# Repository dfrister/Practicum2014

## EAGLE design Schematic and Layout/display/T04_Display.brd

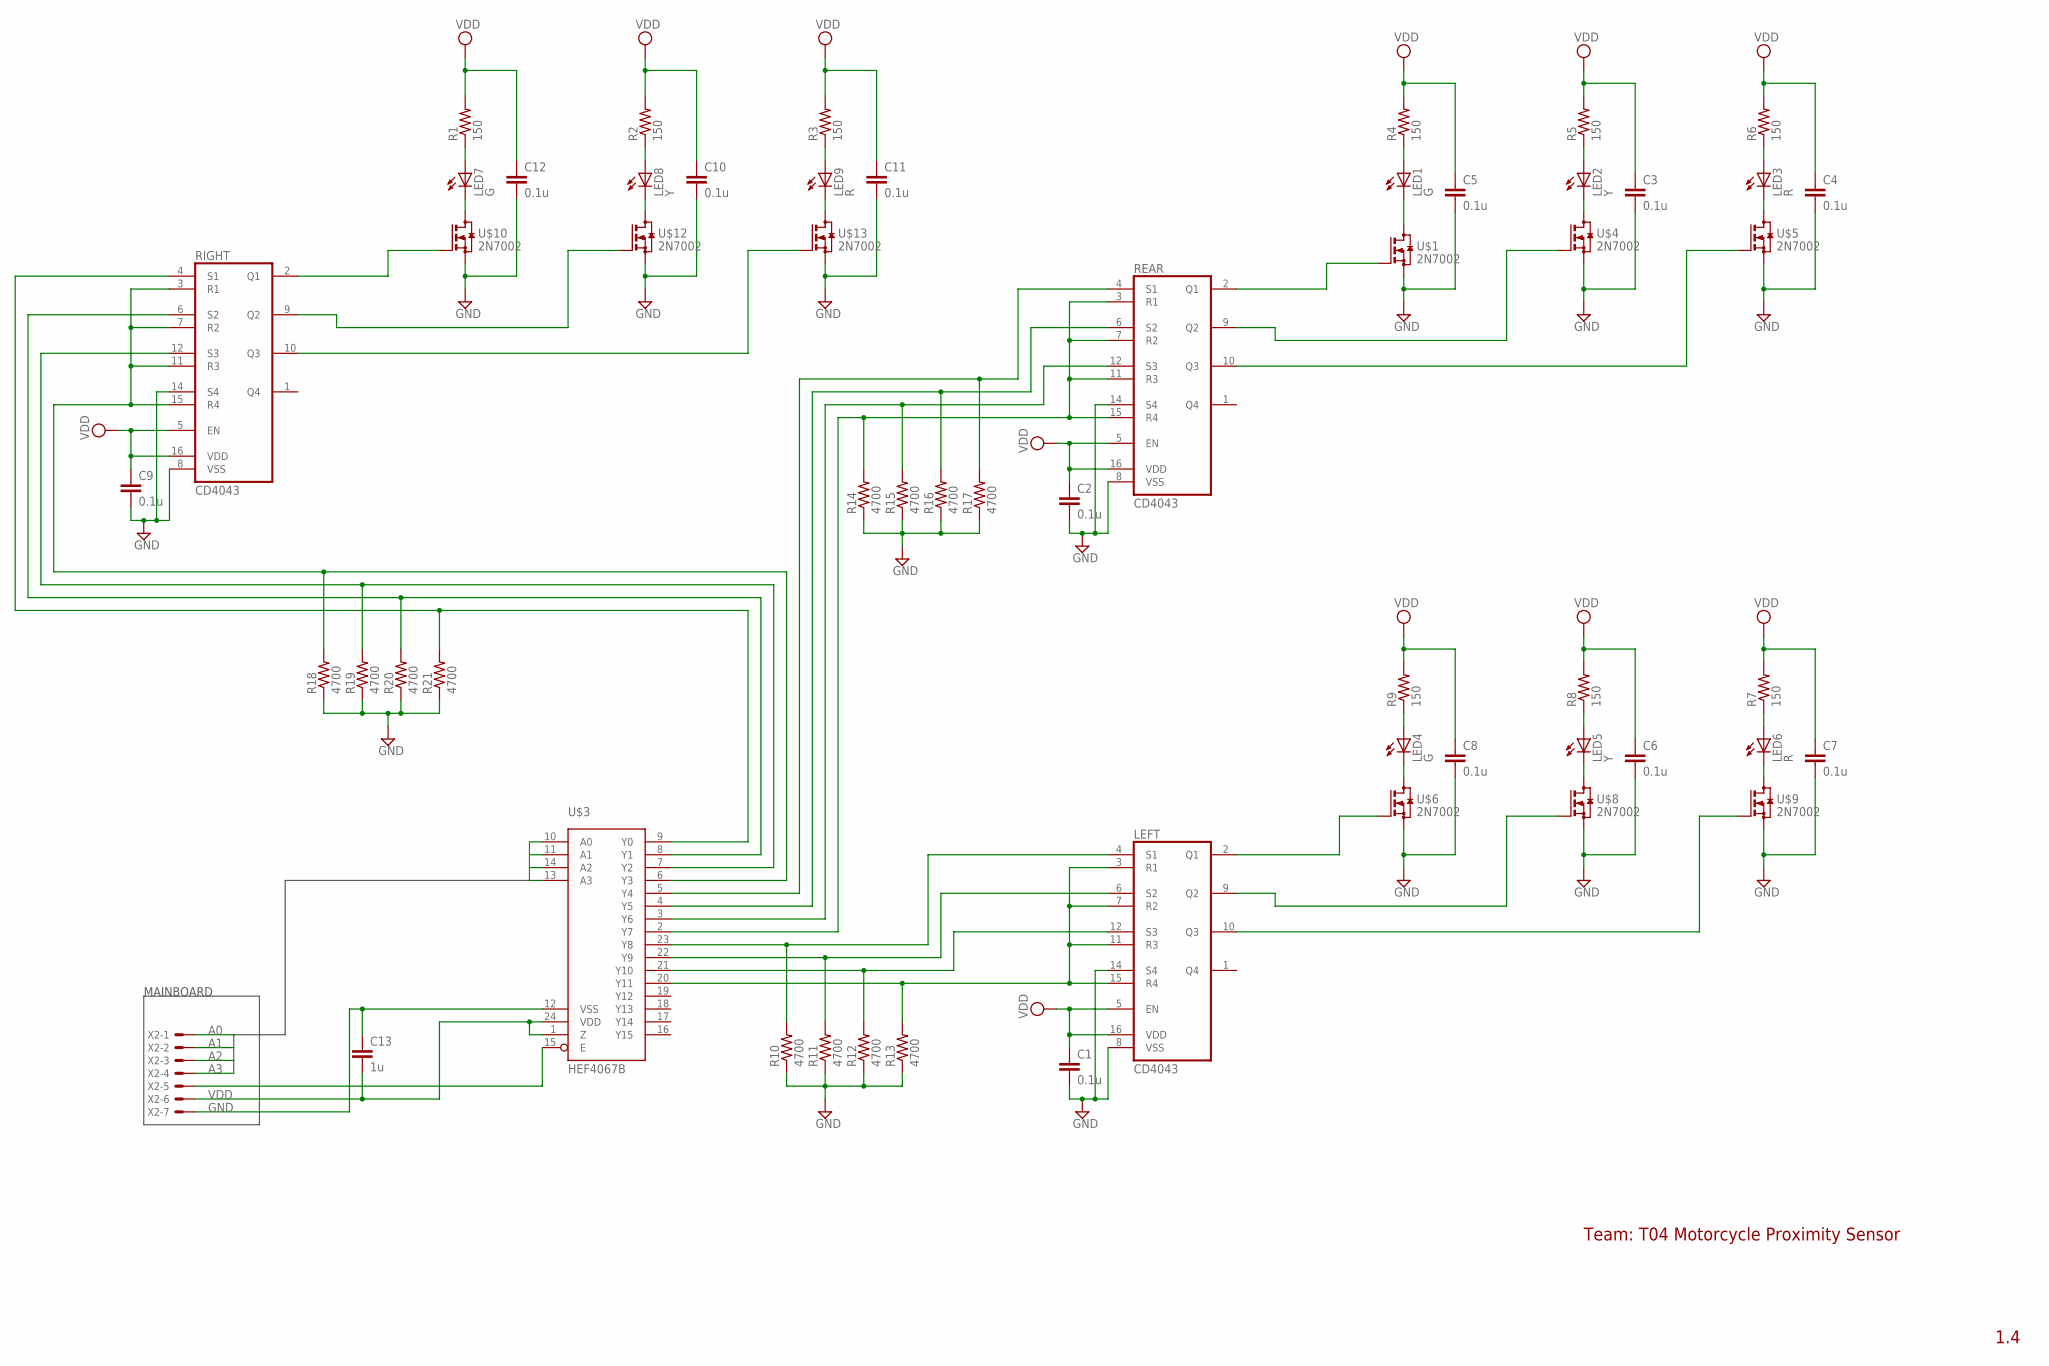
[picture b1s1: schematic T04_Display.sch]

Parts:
C1, C2, C3, C4, C5, C6, C7, C8, C9, C10, C11, C12: 0.1u; C1206
C13: 1u; C1206
LED1, LED4, LED7: G; LED3MM
LED2, LED5, LED8: Y; LED3MM
LED3, LED6, LED9: R; LED3MM
LEFT: CD4043; SOIC16N
R1, R2, R3, R4, R5, R6, R7, R8, R9: 150; R1206
R10, R11, R12, R13, R14, R15, R16, R17, R18, R19, R20, R21: 4700; R1206
REAR: CD4043; SOIC16N
RIGHT: CD4043; SOIC16N
U$1, U$4, U$5, U$6, U$8, U$9, U$10, U$12, U$13: 2N7002; SOT23
U$3: HEF4067B; SO24W
X2: 22-23-2071

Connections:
A0: U$3.10 (A0), X2.1
A1: U$3.11 (A1), X2.2
A2: U$3.14 (A2), X2.3
A3: U$3.13 (A3), X2.4
BG: RIGHT.2 (Q1), U$10.1 (G)
BR: RIGHT.10 (Q3), U$13.1 (G)
BRES: R18.2, RIGHT.3 (R1), RIGHT.7 (R2), RIGHT.11 (R3), RIGHT.15 (R4), U$3.6 (Y3)
BS1: R21.2, RIGHT.4 (S1), U$3.9 (Y0)
BS2: R20.2, RIGHT.6 (S2), U$3.8 (Y1)
BS3: R19.2, RIGHT.12 (S3), U$3.7 (Y2)
BY: RIGHT.9 (Q2), U$12.1 (G)
GND: C1.2, C2.2, C3.2, C4.2, C5.2, C6.2, C7.2, C8.2, C9.2, C10.2, C11.2, C12.2, C13.1, LEFT.8 (VSS), LEFT.14 (S4), R10.1, R11.1, R12.1, R13.1, R14.1, R15.1, R16.1, R17.1, R18.1, R19.1, R20.1, R21.1, REAR.8 (VSS), REAR.14 (S4), RIGHT.8 (VSS), RIGHT.14 (S4), U$1.2 (S), U$3.12 (VSS), U$4.2 (S), U$5.2 (S), U$6.2 (S), U$8.2 (S), U$9.2 (S), U$10.2 (S), U$12.2 (S), U$13.2 (S), X2.7
LG: REAR.2 (Q1), U$1.1 (G)
LR: REAR.10 (Q3), U$5.1 (G)
LRES: R14.2, REAR.3 (R1), REAR.7 (R2), REAR.11 (R3), REAR.15 (R4), U$3.2 (Y7)
LS1: R17.2, REAR.4 (S1), U$3.5 (Y4)
LS2: R16.2, REAR.6 (S2), U$3.4 (Y5)
LS3: R15.2, REAR.12 (S3), U$3.3 (Y6)
LY: REAR.9 (Q2), U$4.1 (G)
unnamed: LED3.K (C), U$5.3 (D)
unnamed: LED2.K (C), U$4.3 (D)
unnamed: LED1.K (C), U$1.3 (D)
unnamed: LED1.A, R4.1
unnamed: LED3.A, R6.1
unnamed: U$3.15 (E), X2.5
unnamed: LED4.A, R9.1
unnamed: LED5.A, R8.1
unnamed: LED2.A, R5.1
unnamed: LED6.A, R7.1
unnamed: LED7.K (C), U$10.3 (D)
unnamed: LED7.A, R1.1
unnamed: LED8.K (C), U$12.3 (D)
unnamed: LED8.A, R2.1
unnamed: LED9.K (C), U$13.3 (D)
unnamed: LED9.A, R3.1
unnamed: LED6.K (C), U$9.3 (D)
unnamed: LED4.K (C), U$6.3 (D)
unnamed: LED5.K (C), U$8.3 (D)
RG: LEFT.2 (Q1), U$6.1 (G)
RR: LEFT.10 (Q3), U$9.1 (G)
RRES: LEFT.3 (R1), LEFT.7 (R2), LEFT.11 (R3), LEFT.15 (R4), R13.2, U$3.20 (Y11)
RS1: LEFT.4 (S1), R10.2, U$3.23 (Y8)
RS2: LEFT.6 (S2), R11.2, U$3.22 (Y9)
RS3: LEFT.12 (S3), R12.2, U$3.21 (Y10)
RY: LEFT.9 (Q2), U$8.1 (G)
VDD: C1.1, C2.1, C3.1, C4.1, C5.1, C6.1, C7.1, C8.1, C9.1, C10.1, C11.1, C12.1, C13.2, LEFT.5 (EN), LEFT.16 (VDD), R1.2, R2.2, R3.2, R4.2, R5.2, R6.2, R7.2, R8.2, R9.2, REAR.5 (EN), REAR.16 (VDD), RIGHT.5 (EN), RIGHT.16 (VDD), U$3.1 (Z), U$3.24 (VDD), X2.6

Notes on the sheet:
MAINBOARD
Team: T04 Motorcycle Proximity Sensor
1.4

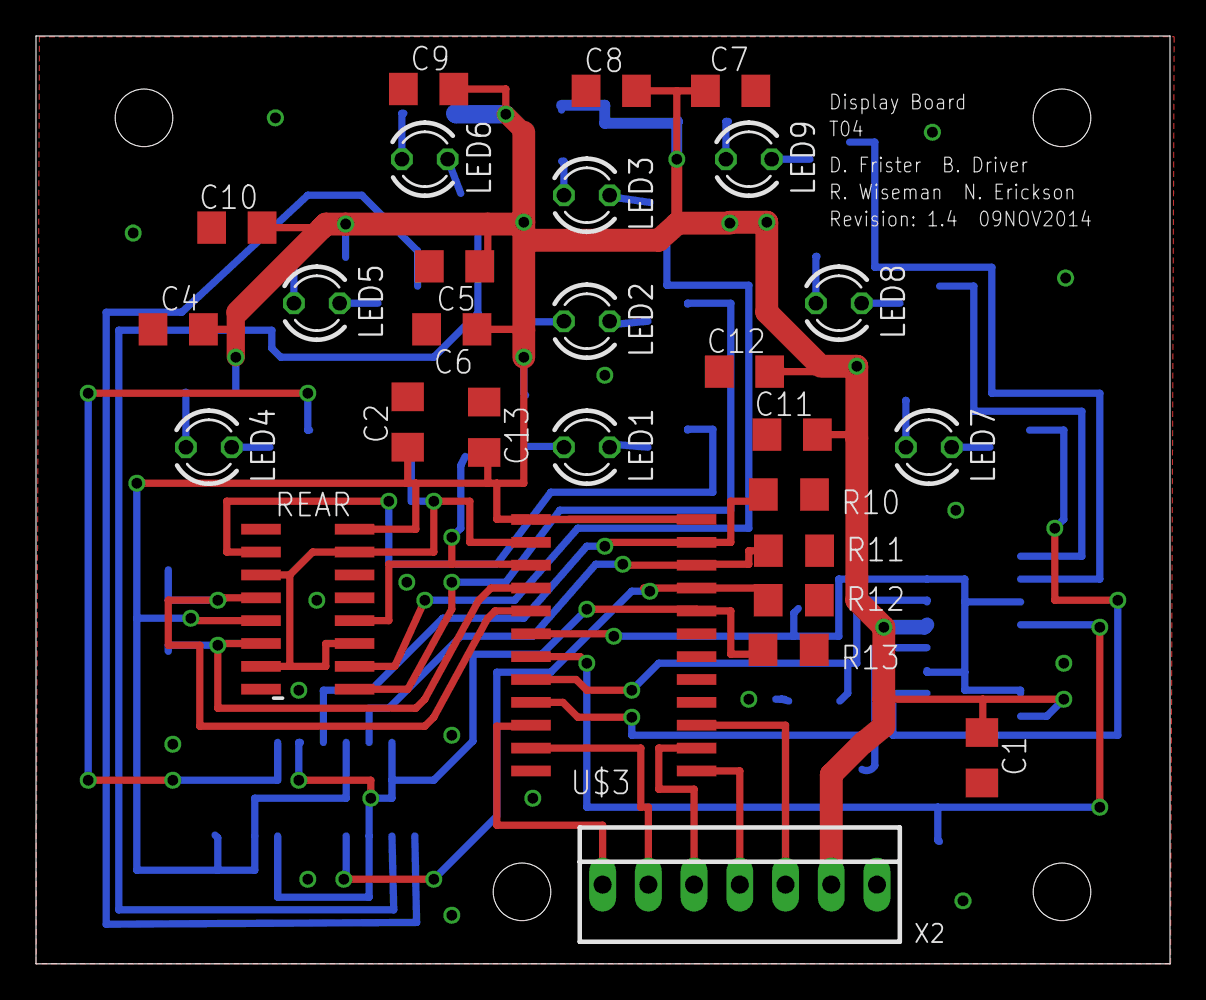
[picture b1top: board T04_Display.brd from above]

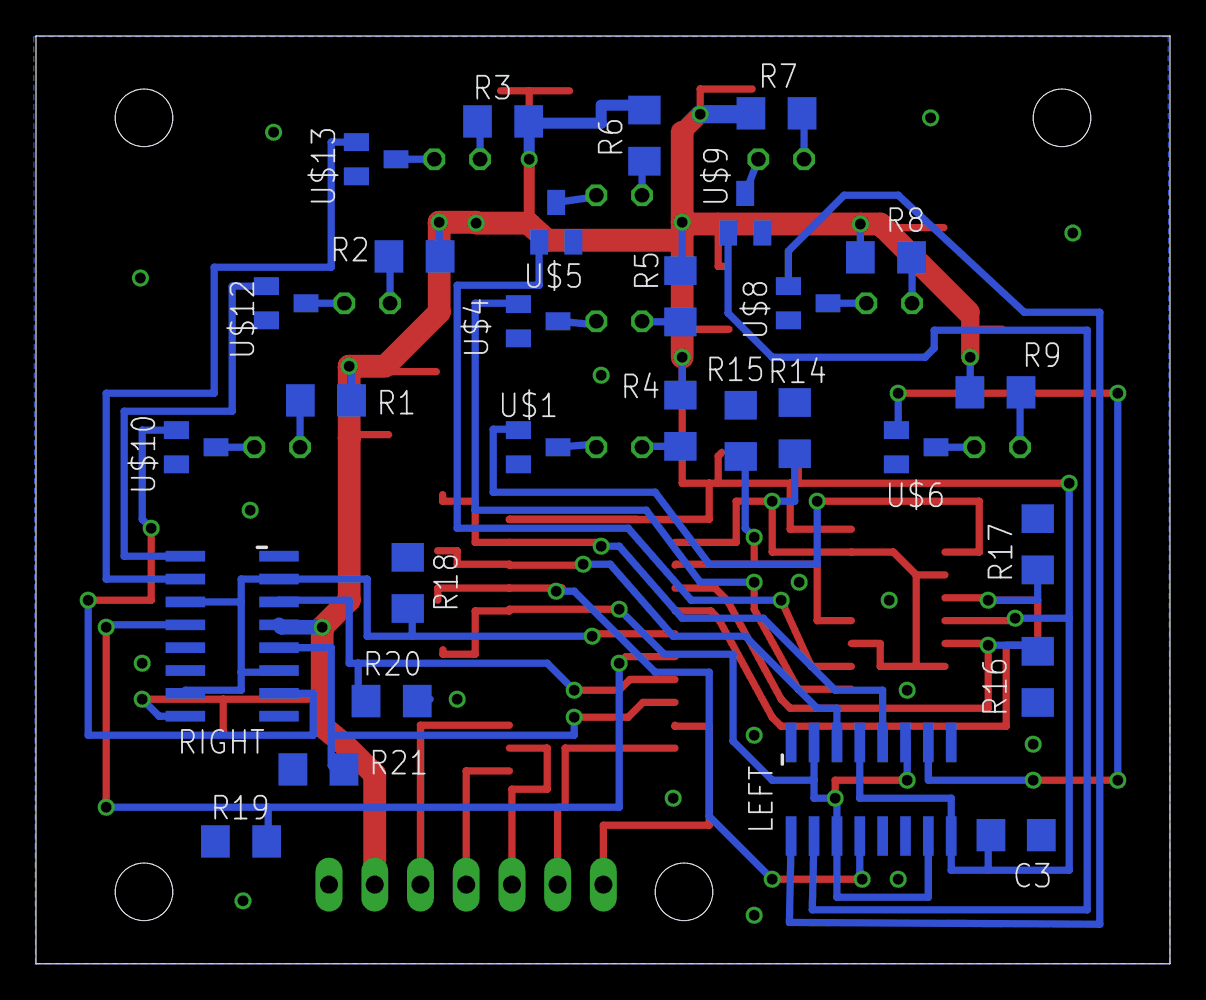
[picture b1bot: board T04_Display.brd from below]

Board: 2 copper layers, 63.0 x 51.5 mm, 57 parts (29 on the bottom side), 46 nets.

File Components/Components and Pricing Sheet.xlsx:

Manufacturer | Part # | Component | Supplier | Price | Qty/Person | Total Qty | Total Price |  | Model |  |  |  |  | Prototype Order 10/26
Lite-On | LTL1CHKGKNN | Green LED | Mouser | 0.107 | 3 | 12 | 1.284 | 3mm | Final |  | Final Build |  |  | Manufacturer | Part # | Component | Supplier | Price | Qty | Total
Lite-On | LTL1CHKEKNN | Red LED | Mouser | 0.09 | 3 | 12 | 1.08 | 3mm | Final |  | Prototype |  |  | Lite-On | LTL1CHKGKNN | Green LED | Mouser | 0.107 | 12 | 1.284
Lite-On | LTL1CHKSKNN | Yellow LED | Mouser | 0.10199999999999999 | 3 | 12 | 1.224 | 3mm | Final |  | Ordered |  |  | Lite-On | LTL1CHKEKNN | Red LED | Mouser | 0.09 | 12 | 1.08
Fairchild | 2n7002DW | Dual N-channel FET | Mouser | 0.27600000000000002 | 5 | 20 | 5.5200000000000005 | smt | Final |  | Substituted |  |  | Lite-On | LTL1CHKSKNN | Yellow LED | Mouser | 0.10199999999999999 | 12 | 1.224
Fairchild | 2n7000 | N-Channel FET | Mouser | 0.24 | 10 | 10 | 2.4 | Thru-Hole | Prototype |  |  |  |  | Fairchild | 2n7000 | N-Channel FET | Mouser | 0.24 | 10 | 2.4
ON-Semiconductor | MC14514BDWR2G | 4-16 demux | Mouser | 1.61 | 1 | 4 | 6.44 | smt | n/a |  |  |  |  | NXP Semiconductor | HEF4067BPN | 4-16 demux | Mouser | 5.43 | 1 | 5.43
ON-Semiconductor | CD4043BE | Quad SR latch | Mouser | 0.6 | 3 | 4 | 2.4 | Thru-Hole | Prototype |  |  |  |  | ON-Semiconductor | CD4043BE | Quad SR latch | Mouser | 0.6 | 4 | 2.4
ON-Semiconductor | CD4043BDWR | Quad SR latch | Mouser | 0.67 | 3 | 12 | 8.0400000000000009 | SMT | final
NXP Semiconductor | HEF4067BPN | 4-16 demux | Mouser | 5.43 | 1 | 1 | 5.43 | Thru-Hole | Prototype
NXP Semiconductor | HEF4067BT | 4-16 demux | Mouser | 2.38 | 1 | 4 | 9.52 | SMT | final |  |  |  |  |  |  |  |  |  | Shipping | 6.99
 |  |  |  |  |  | 0 | 0
 |  |  |  |  |  | 0 | 0
 |  |  |  |  |  | 0 | 0
 |  |  |  |  |  | 0 | 0 |  |  |  |  |  |  |  |  |  |  |  |  | 20.808
 |  |  |  |  |  | 0 | 0
 |  |  |  |  |  | 0 | 0

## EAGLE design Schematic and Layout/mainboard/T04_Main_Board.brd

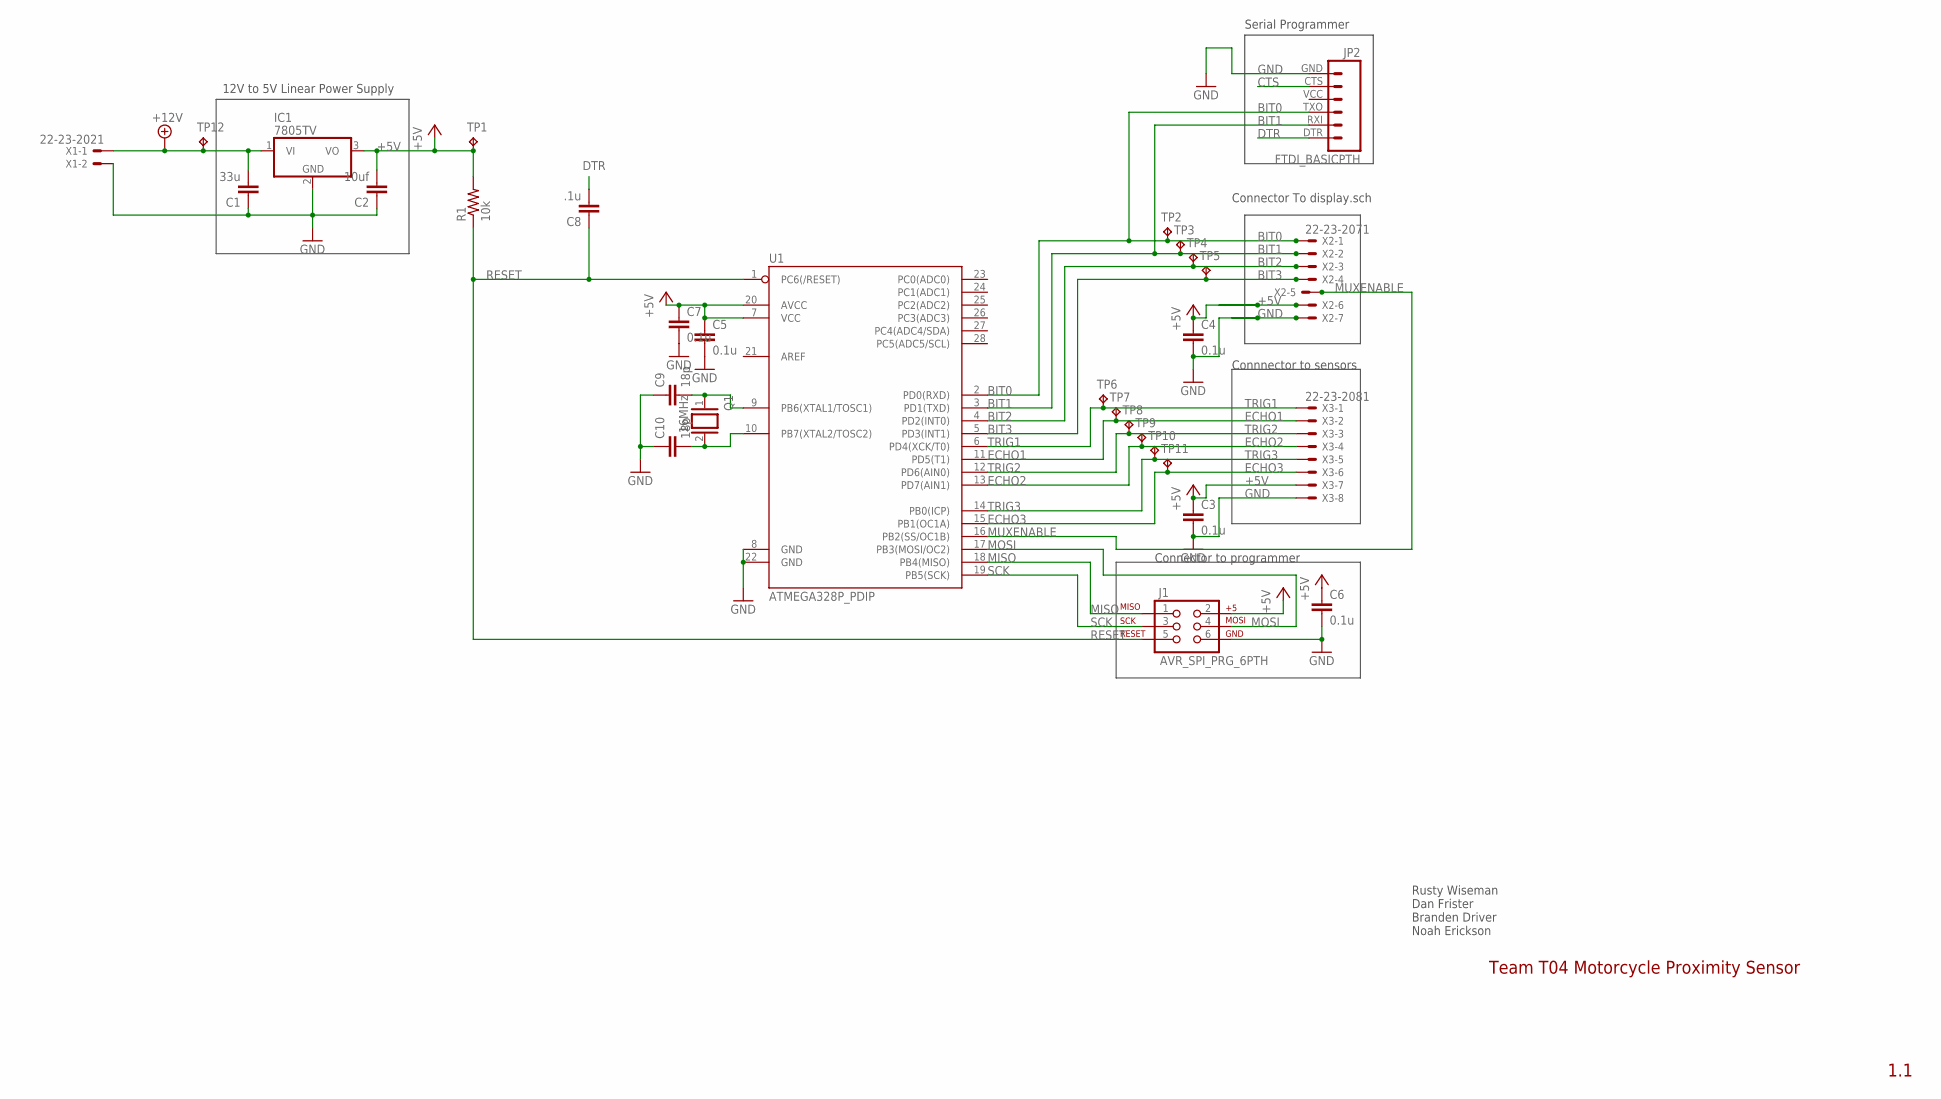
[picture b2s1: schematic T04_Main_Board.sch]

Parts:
C1: 33u; C1206
C2: 10uf; C1206
C3, C4, C5, C6, C7: 0.1u; C1206
C8: .1u; C1206
C9, C10: 18p; C1206
IC1: 7805TV; TO220V
J1: AVR_SPI_PRG_6PTH; 2X3
JP2: FTDI_BASICPTH; FTDI_BASIC
Q1: 16MHz; QS
R1: 10k; R1206
TP1, TP2, TP3, TP4, TP5, TP6, TP7, TP8, TP9, TP10, TP11, TP12: TPB1,27; B1,27
U1: ATMEGA328P_PDIP; DIL28-3
X1: 22-23-2021
X2: 22-23-2071
X3: 22-23-2081

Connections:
+5V: C2.2, C3.1, C4.1, C5.1, C6.1, C7.1, IC1.3 (VO), J1.2, R1.2, TP1.TP, U1.7 (VCC), U1.20 (AVCC), X2.6, X3.7
+12V: C1.2, IC1.1 (VI), TP12.TP, X1.1
BIT0: JP2.TXO (3), TP2.TP, U1.2 (PD0(RXD)), X2.1
BIT1: JP2.RXI (2), TP3.TP, U1.3 (PD1(TXD)), X2.2
BIT2: TP4.TP, U1.4 (PD2(INT0)), X2.3
BIT3: TP5.TP, U1.5 (PD3(INT1)), X2.4
CTS: JP2.CTS (5)
DTR: C8.2, JP2.DTR (1)
ECHO1: TP7.TP, U1.11 (PD5(T1)), X3.2
ECHO2: TP9.TP, U1.13 (PD7(AIN1)), X3.4
ECHO3: TP11.TP, U1.15 (PB1(OC1A)), X3.6
GND: C1.1, C2.1, C3.2, C4.2, C5.2, C6.2, C7.2, C9.1, C10.1, IC1.2 (GND), J1.6, JP2.GND (6), U1.8 (GND), U1.22 (GND), X1.2, X2.7, X3.8
MISO: J1.1, U1.18 (PB4(MISO))
MOSI: J1.4, U1.17 (PB3(MOSI/OC2))
MUXENABLE: U1.16 (PB2(SS/OC1B)), X2.5
unnamed: C10.2, Q1.2, U1.10 (PB7(XTAL2/TOSC2))
unnamed: C9.2, Q1.1, U1.9 (PB6(XTAL1/TOSC1))
RESET: C8.1, J1.5, R1.1, U1.1 (PC6(/RESET))
SCK: J1.3, U1.19 (PB5(SCK))
TRIG1: TP6.TP, U1.6 (PD4(XCK/T0)), X3.1
TRIG2: TP8.TP, U1.12 (PD6(AIN0)), X3.3
TRIG3: TP10.TP, U1.14 (PB0(ICP)), X3.5

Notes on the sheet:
12V to 5V Linear Power Supply
Connector To display.sch
Team T04 Motorcycle Proximity Sensor
1.1
Rusty Wiseman Dan Frister Branden Driver Noah Erickson
Connnector to sensors
Connector to programmer
Serial Programmer

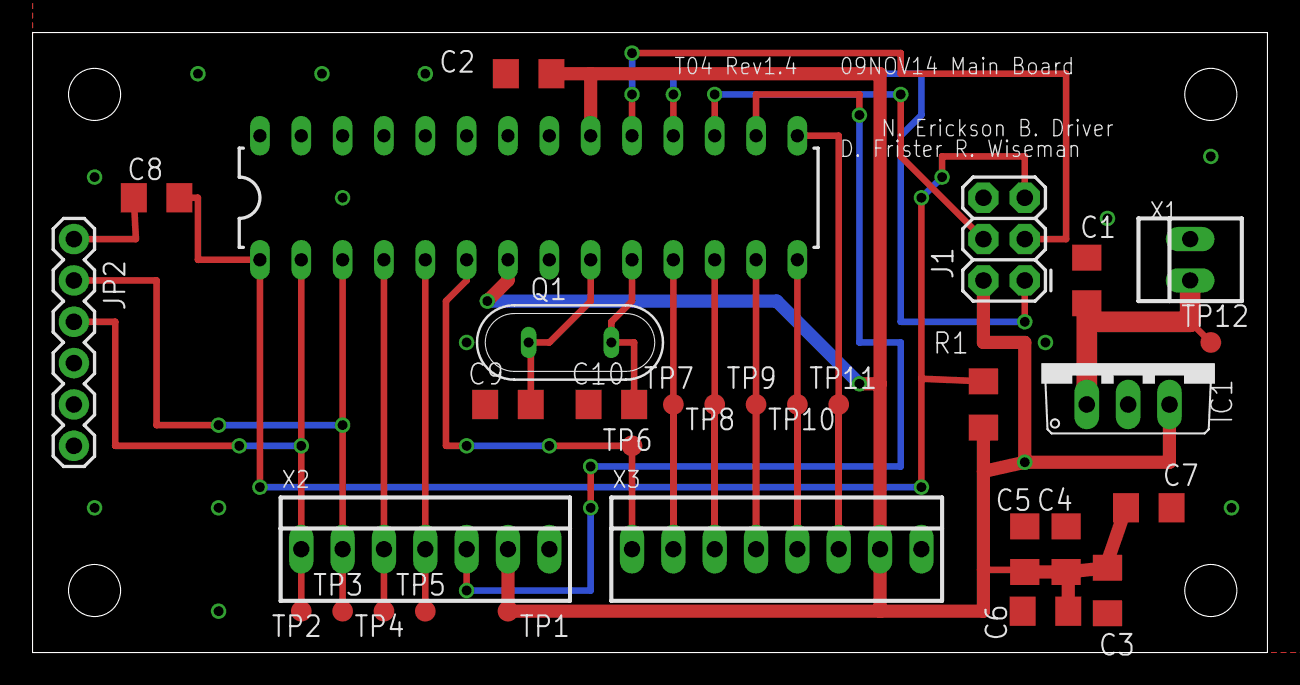
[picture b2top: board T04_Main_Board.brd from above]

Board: 2 copper layers, 75.9 x 38.1 mm, 31 parts (0 on the bottom side), 21 nets.

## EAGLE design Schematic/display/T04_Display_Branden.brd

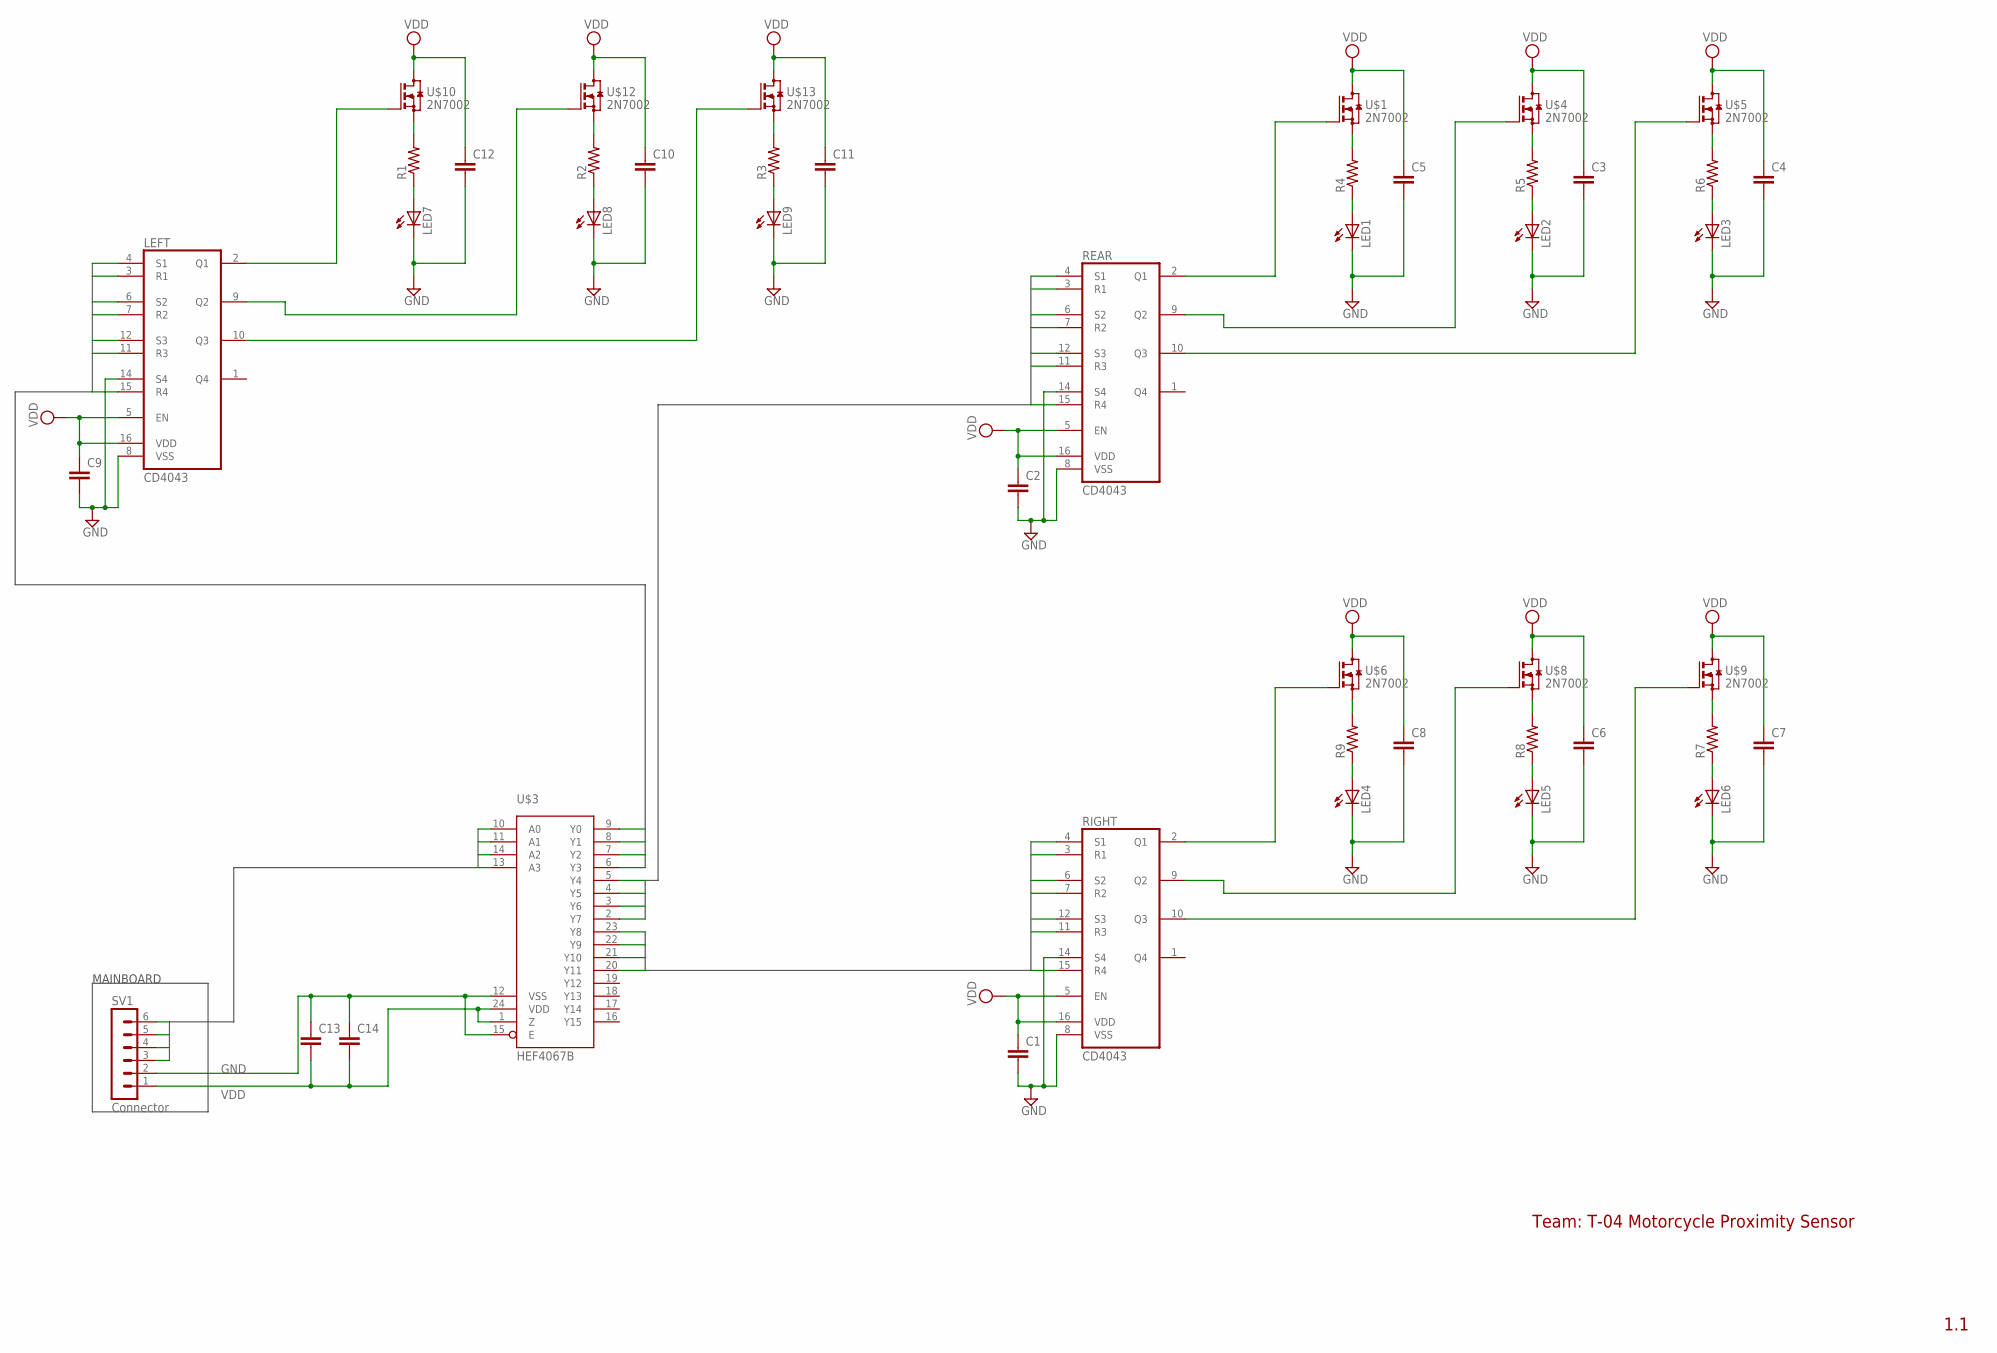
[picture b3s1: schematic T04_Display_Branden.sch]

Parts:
C1, C2, C3, C4, C5, C6, C7, C8, C9, C10, C11, C12, C13, C14: C-EUC1206; C1206
LED1, LED2, LED3, LED4, LED5, LED6, LED7, LED8, LED9: LED3MM
LEFT: CD4043; SOIC16N
R1, R2, R3, R4, R5, R6, R7, R8, R9: R-US_R1206; R1206
REAR: CD4043; SOIC16N
RIGHT: CD4043; SOIC16N
SV1: Connector; MA06-1
U$1, U$4, U$5, U$6, U$8, U$9, U$10, U$12, U$13: 2N7002; SOT23
U$3: HEF4067B; SO24W

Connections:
A0: SV1.6, U$3.10 (A0)
A1: SV1.5, U$3.11 (A1)
A2: SV1.4, U$3.14 (A2)
A3: SV1.3, U$3.13 (A3)
BG: LEFT.2 (Q1), U$10.1 (G)
BR: LEFT.10 (Q3), U$13.1 (G)
BRES: LEFT.3 (R1), LEFT.7 (R2), LEFT.11 (R3), LEFT.15 (R4), U$3.6 (Y3)
BS1: LEFT.4 (S1), U$3.9 (Y0)
BS2: LEFT.6 (S2), U$3.8 (Y1)
BS3: LEFT.12 (S3), U$3.7 (Y2)
BY: LEFT.9 (Q2), U$12.1 (G)
GND: C1.2, C2.2, C3.2, C4.2, C5.2, C6.2, C7.2, C8.2, C9.2, C10.2, C11.2, C12.2, C13.1, C14.1, LED1.K (C), LED2.K (C), LED3.K (C), LED4.K (C), LED5.K (C), LED6.K (C), LED7.K (C), LED8.K (C), LED9.K (C), LEFT.8 (VSS), LEFT.14 (S4), REAR.8 (VSS), REAR.14 (S4), RIGHT.8 (VSS), RIGHT.14 (S4), SV1.2, U$3.12 (VSS), U$3.15 (E)
LG: REAR.2 (Q1), U$1.1 (G)
LR: REAR.10 (Q3), U$5.1 (G)
LRES: REAR.3 (R1), REAR.7 (R2), REAR.11 (R3), REAR.15 (R4), U$3.2 (Y7)
LS1: REAR.4 (S1), U$3.5 (Y4)
LS2: REAR.6 (S2), U$3.4 (Y5)
LS3: REAR.12 (S3), U$3.3 (Y6)
LY: REAR.9 (Q2), U$4.1 (G)
unnamed: R5.2, U$4.2 (S)
unnamed: R8.2, U$8.2 (S)
unnamed: R6.2, U$5.2 (S)
unnamed: R4.2, U$1.2 (S)
unnamed: LED1.A, R4.1
unnamed: LED3.A, R6.1
unnamed: R9.2, U$6.2 (S)
unnamed: LED4.A, R9.1
unnamed: LED5.A, R8.1
unnamed: LED2.A, R5.1
unnamed: R7.2, U$9.2 (S)
unnamed: LED6.A, R7.1
unnamed: R1.2, U$10.2 (S)
unnamed: LED7.A, R1.1
unnamed: R2.2, U$12.2 (S)
unnamed: LED8.A, R2.1
unnamed: R3.2, U$13.2 (S)
unnamed: LED9.A, R3.1
RG: RIGHT.2 (Q1), U$6.1 (G)
RR: RIGHT.10 (Q3), U$9.1 (G)
RRES: RIGHT.3 (R1), RIGHT.7 (R2), RIGHT.11 (R3), RIGHT.15 (R4), U$3.20 (Y11)
RS1: RIGHT.4 (S1), U$3.23 (Y8)
RS2: RIGHT.6 (S2), U$3.22 (Y9)
RS3: RIGHT.12 (S3), U$3.21 (Y10)
RY: RIGHT.9 (Q2), U$8.1 (G)
VDD: C1.1, C2.1, C3.1, C4.1, C5.1, C6.1, C7.1, C8.1, C9.1, C10.1, C11.1, C12.1, C13.2, C14.2, LEFT.5 (EN), LEFT.16 (VDD), REAR.5 (EN), REAR.16 (VDD), RIGHT.5 (EN), RIGHT.16 (VDD), SV1.1, U$1.3 (D), U$3.1 (Z), U$3.24 (VDD), U$4.3 (D), U$5.3 (D), U$6.3 (D), U$8.3 (D), U$9.3 (D), U$10.3 (D), U$12.3 (D), U$13.3 (D)

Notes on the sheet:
MAINBOARD
Team: T-04 Motorcycle Proximity Sensor
1.1

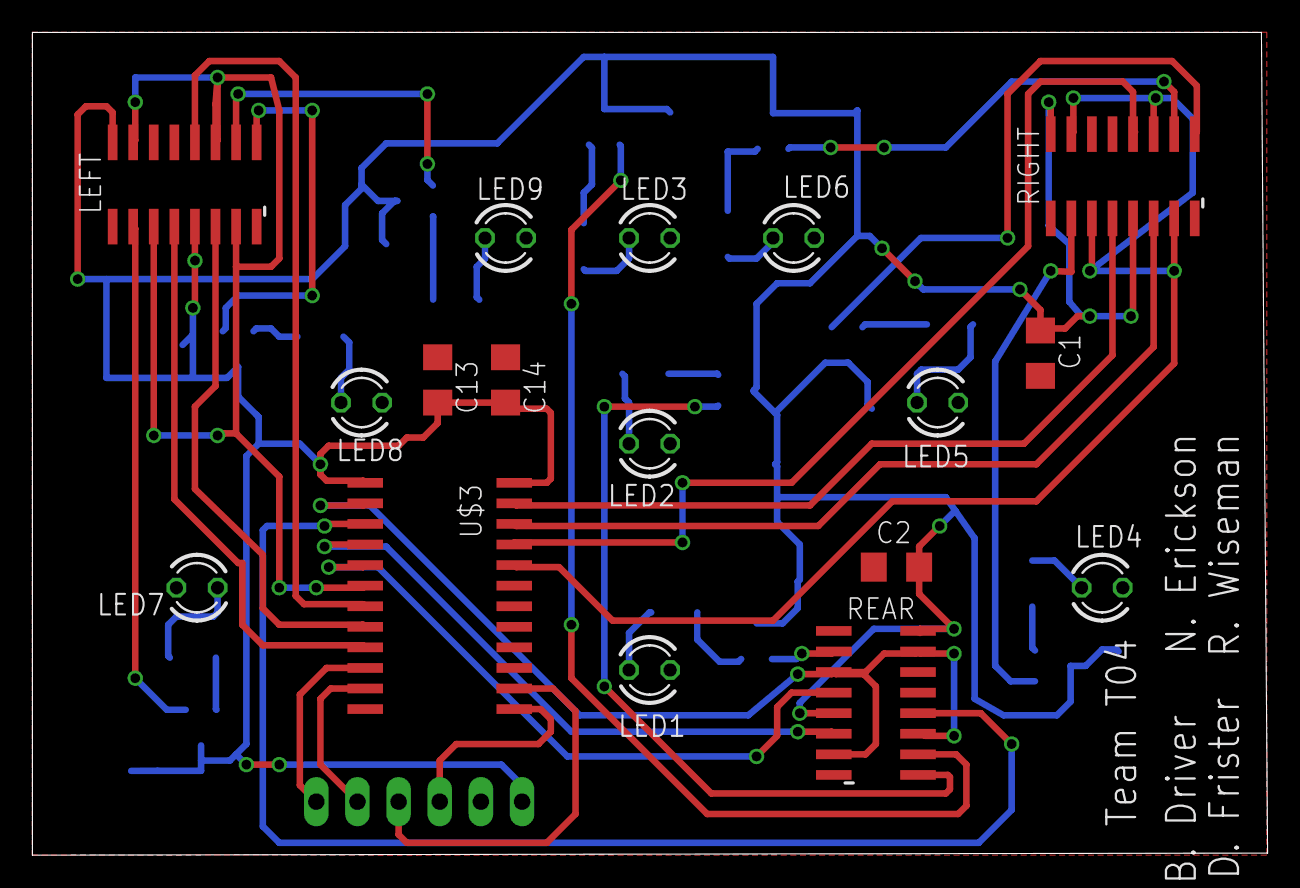
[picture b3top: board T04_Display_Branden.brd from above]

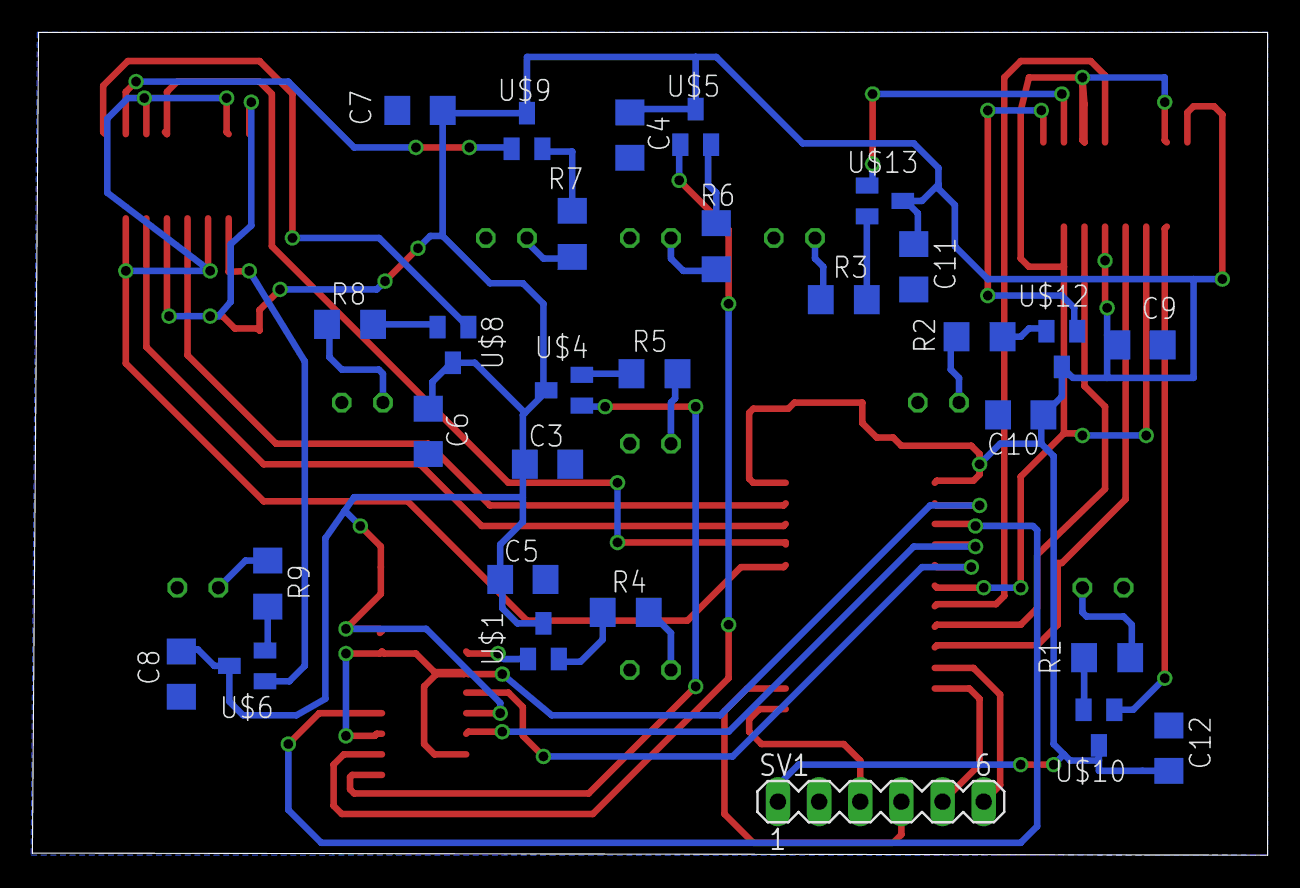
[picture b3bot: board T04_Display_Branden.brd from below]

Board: 2 copper layers, 76.3 x 50.8 mm, 46 parts (29 on the bottom side), 45 nets.

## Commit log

2014-10-08 Create License
    Required addition of license for project, as per meeting 08OCT14.
2014-10-12 Project files for 13OCT14 assignment. Decision Matrix based on coursework text appendix B and examples on page 22. Subjective weighting values for decisions based on discussions of each project durin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
2014-10-12 Concept Art for title Page
2014-10-12 Size Modified on Concept
2014-10-13 test
2014-10-13 untest
2014-10-13 branch test
2014-10-13 Delete forktest.txt
    Test failed, delete
2014-10-13 Added matrix description to matrix doc and added header and names to others. Ready to print and turn in.
2014-10-13 Fixed Proposal Title
2014-10-16 Initial Schematic
2014-10-20 Requirements Specifications Added
2014-10-20 Schematic Update
2014-10-21 Schematic update and meeting notes
2014-10-22 Breadboard Prototype
2014-10-22 Working Prototype
2014-10-24 New folder for components
2014-10-24 Added component spreadsheet and datasheets for leds, fets, and demux
2014-10-24 Again
2014-10-24 Basic layout of display circuit. Componant values and part numbers require update. Still needs interface to main board.
2014-10-25 prototype_code_rev2
2014-10-25 Mainboard schematic
2014-10-25 Finished draft of Requirements Specifications.
2014-10-26 Prototype Code Update
2014-10-26 New datasheets and updated components spreadsheet with new components and prototype parts order.
2014-10-26 Prototype 2 w/ 2 Sensors
2014-10-26 Prototype rev3 with 2 sensors
2014-10-26 Prototype rev3 with 2 sensors (fixed)
2014-10-27 Final draft of hw3.
2014-10-28 Prototype_rev4 added, schematic update. Also fixed old prototypes being overwritten, oops.
2014-10-28 prototype_rev4 (fix)
2014-10-29 Finalized V1.0 Schematics for assignment.
2014-10-29 Rename mainboard.sch to T04_Main_Board.sch
2014-10-29 Rename display.sch to T04_Display.sch
2014-10-29 ERC Update Display Schematic
2014-10-30 Mainboard Update and Prototype_rev4 update
2014-10-30 Logo
2014-10-31 Board Layout Rev1
2014-10-31 Deleted # saved files
2014-10-31 V1.1 Schematic, with latches
2014-11-01 Preliminary Board Layout Rev.1
2014-11-01 Deleted # files
2014-11-01 Udpated layout with team names on board and more clearly labeled component names
2014-11-01 New datasheets for latch,mux.
2014-11-02 Code update
2014-11-04 Mainboard update - Clock and bypass caps
2014-11-04 Mainboard - Added mounting holes
2014-11-05 Fixed DRC errors on C3.
2014-11-05 Mainboard layout fixed
2014-11-05 Reverified ERC/DRC for assignment files, added version summery.
2014-11-05 Update Design_Version_Summery.txt
    Modified Display 1.1 description.
2014-11-06 Delete 2n7002dw dual fet.pdf
    Trimming datasheets not being used.
2014-11-06 Delete DEMUX_MC14514B-D-23584.pdf
    Trimming datasheets not being used.
2014-11-06 Delete MM74HC4514.pdf
    Trimming datasheets not being used.
2014-11-07 Mainboard & Display layout updates - Molex connectors, Mounting Holes, Greenberg Email Additions
2014-11-08 Updated Schematic and Revision text to match instructor review.
2014-11-09 Updated display board
2014-11-09 Second layout option for display using enable pins and smaller area.
2014-11-09 PR0T0TYP3 C0MP73T3
2014-11-09 M@INb0@RD C0MPl37e
2014-11-09 3V3RY7H1NG 15 C0MPl373
2014-11-09 Rev 1.5 of display board. Still needs updated mulex connector
2014-11-09 Fixed drc error from previous committ
2014-11-09 Display w/ 7-pin molex
2014-11-09 Finished project schedule, posting for review.
2014-11-09 Mainboard Rev 1.3 Update
2014-11-09 Rev 1.4 Schematics/Layouts
2014-11-09 Final Schematic - Mainboard
2014-11-09 Final Revision for display before submit.
2014-11-10 File Cleanup
2014-11-10 Submitted Files to OSHpark, updated versions.
2014-11-10 Branden's display design
2014-11-10 Revision History for Display update.
2014-11-10 Revision for schedule
2014-11-15 First Draft state diagram for UML assignment.
2014-11-15 Initial Interactive View
2014-11-17 Pushing System Design and Modeling.pdf homework assignment. Complete.
2014-11-17 Added team number to file.
2014-11-18 Uploaded sensor enclosure drawings, pdf and svg.
2014-11-18 Updated project schedule
2014-11-21 Updated drawing for three enclosures
2014-11-22 Updated version of sensor enclosure. DON'T USE YET!!
2014-11-23 COMMIT NUMBER 100
2014-11-23 Revision History
2014-11-23 Test plan minus test cases
2014-11-23 TestCaseMainboard1
2014-11-23 Test case for demux
2014-11-23 Completed review of complete test plan, added power test for display. Added test plan for integration 1. Moved Hello World test plan to xlsx format properly. Updated revision numbers.
2014-11-23 File cleanup.
2014-11-23 Brandon's Display Enclosure Rev1.0/Bottom_Piece.pdf(Rev1) and my Display Enclosure (Rev2)
2014-11-24 System Test Plan added
2014-11-24 Finalized versions of test plans (formatted) and complete assignment pdf.
2014-11-24 Fixed display board version numbers.
2014-11-24 Added team number to title page, spelling revisions.
2014-11-24 Section 3.0 Revision
2014-11-29 revised display rev2 to pieces for three enclosures.
2014-11-30 Rev2.1
2014-12-05 Code header matches schematic header
2014-12-06 LED iteration code
2014-12-07 Updated binary and timing
2014-12-08 Updated enclosures. Use Mainboard Enclosure_V2.svg.
2014-12-08 Updated final code
2014-12-09 Initial Presentation
2014-12-10 Updated Prototype code for long range Began powerpoint
2014-12-10 uploaded Presentation Outline.docx
2014-12-10 Code update, no timing, 15,10,5 distances
2014-12-11 Code organization
2014-12-11 Final Code
2014-12-11 Presentation update
2014-12-11 Updated presentation
2014-12-11 Cleaned up final code
2014-12-11 Presentation title update
2014-12-12 this is actually Noah fixing the powerpoint!
2014-12-12 noah again!
2014-12-12 spalt batter

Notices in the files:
parts and their libraries:
SparkFun-Connectors: Licensing: Creative Commons ShareAlike 4.0 International - https://creativecommons.org/licenses/by-sa/4.0
